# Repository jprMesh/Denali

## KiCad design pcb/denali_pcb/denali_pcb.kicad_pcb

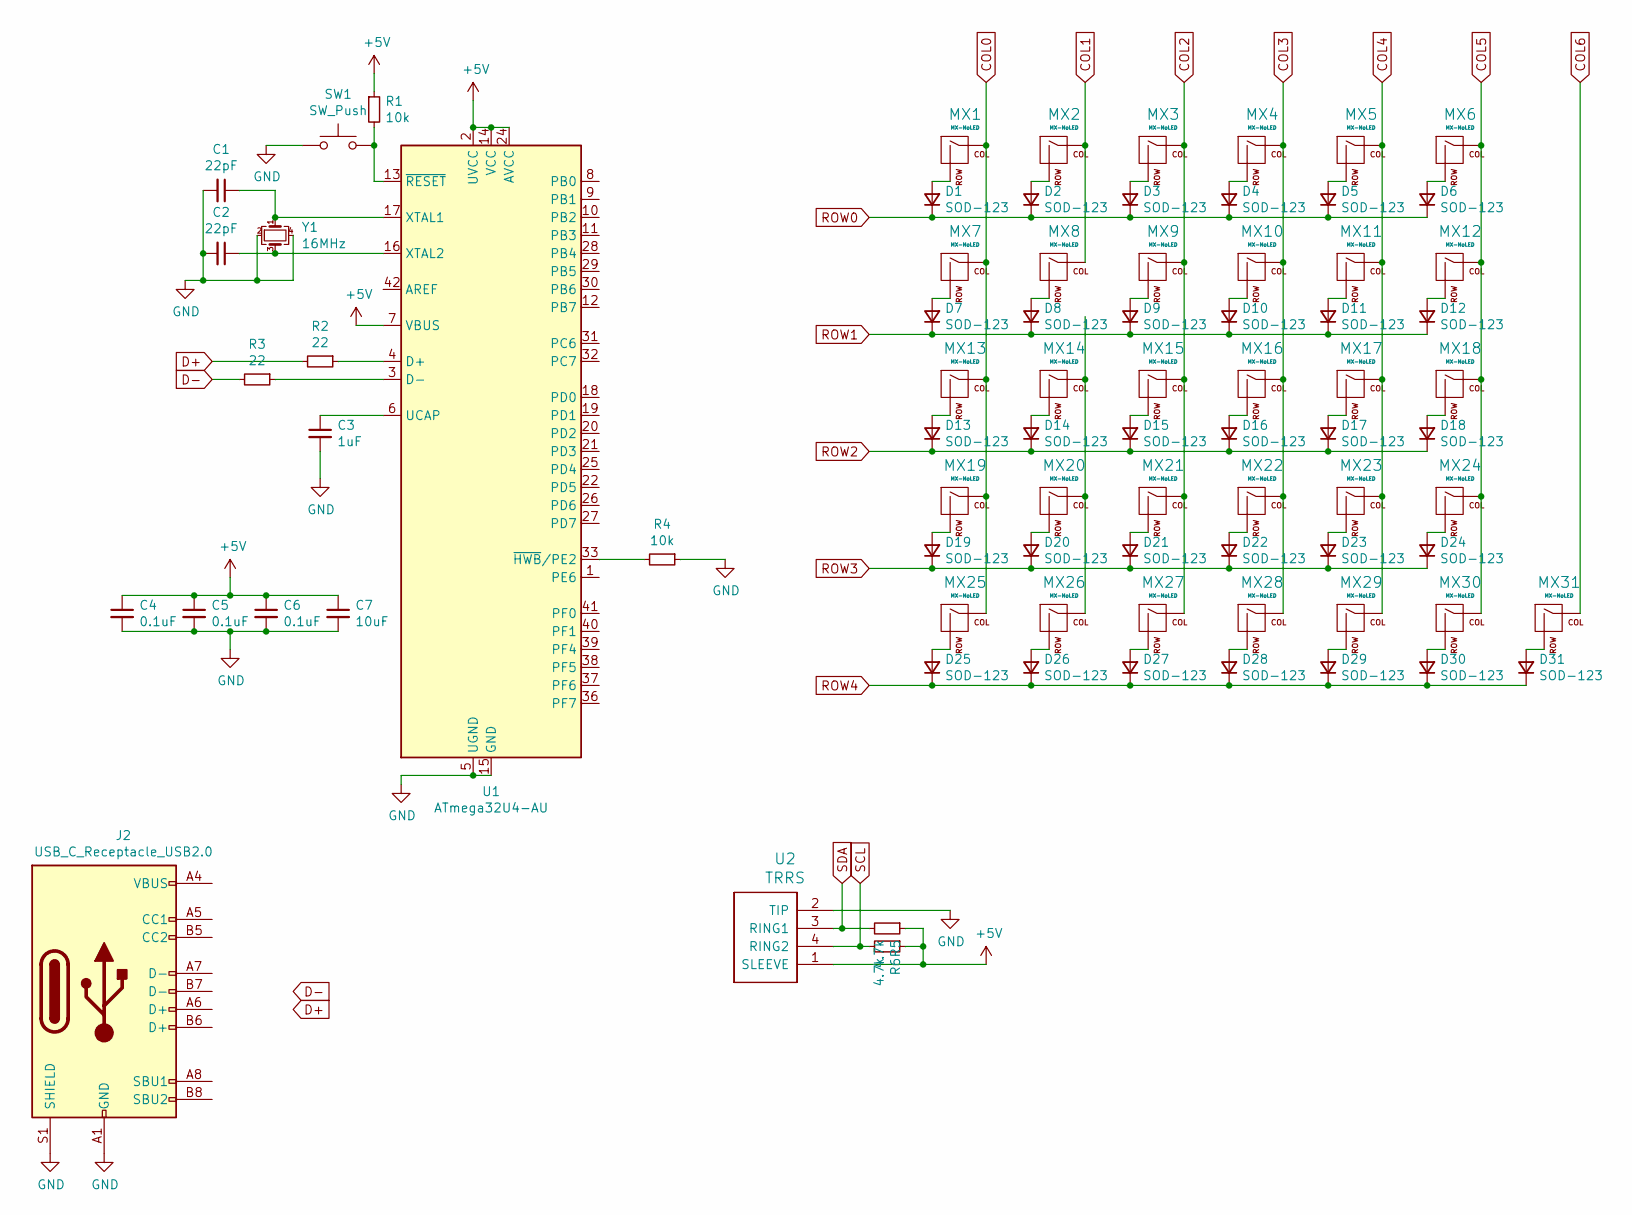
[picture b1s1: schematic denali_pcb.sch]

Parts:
C1, C2: 22pF; C_0805_2012Metric
C3: 1uF; C_0805_2012Metric
C4, C5, C6: 0.1uF; C_0805_2012Metric
C7: 10uF; C_0805_2012Metric
D1, D2, D3, D4, D5, D6, D7, D8, D9, D10, D11, D12, D13, D14, D15, D16, D17, D18, D19, D20, D21, D22, D23, D24, D25, D26, D27, D28, D29, D30, D31: SOD-123; Diode-hybrid-3pad
J2: USB_C_Receptacle_USB2.0; USB_C_Receptacle_MUP_U22401
MX1, MX2, MX3, MX4, MX5, MX6, MX7, MX8, MX9, MX10, MX11, MX12, MX13, MX14, MX15, MX16, MX17, MX18, MX19, MX20, MX21, MX22, MX23, MX24, MX25, MX26, MX27, MX28, MX29, MX30, MX31: MX-NoLED; Kailh_socket_PG1350_reversible
R1, R4: 10k; R_0805_2012Metric
R2, R3: 22; R_0805_2012Metric
R5, R6: 4.7k; R_0805_2012Metric
SW1: SW_Push; SKQG-1155865
U1: ATmega32U4-AU; TQFP-44_10x10mm_P0.8mm
U2: TRRS; TRRS-PJ-320A-dual
Y1: 16MHz; Crystal_SMD_3225-4Pin_3.2x2.5mm_HandSoldering

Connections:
+5V: C4.1, C5.1, C6.1, C7.1, R1.1, R5.1, R6.1, U1.2 (UVCC), U1.7 (VBUS), U1.14 (VCC), U1.24 (AVCC), U1.34 (VCC), U1.44 (AVCC), U2.1 (SLEEVE)
COL0: MX1.1 (COL), MX7.1 (COL), MX13.1 (COL), MX19.1 (COL), MX25.1 (COL)
COL1: MX2.1 (COL), MX8.1 (COL)
COL2: MX3.1 (COL), MX9.1 (COL), MX15.1 (COL), MX21.1 (COL), MX27.1 (COL)
COL3: MX4.1 (COL), MX10.1 (COL), MX16.1 (COL), MX22.1 (COL), MX28.1 (COL)
COL4: MX5.1 (COL), MX11.1 (COL), MX17.1 (COL), MX23.1 (COL), MX29.1 (COL)
COL5: MX6.1 (COL), MX12.1 (COL), MX18.1 (COL), MX24.1 (COL), MX30.1 (COL)
COL6: MX31.1 (COL)
D+: R2.2
D-: R3.2
GND: C1.2, C2.2, C3.2, C4.2, C5.2, C6.2, C7.2, J2.A1 (GND), J2.A12 (GND), J2.B1 (GND), J2.B12 (GND), J2.S1 (SHIELD), R4.1, SW1.1, U1.5 (UGND), U1.15 (GND), U1.23 (GND), U1.35 (GND), U1.43 (GND), U2.2 (TIP), Y1.2, Y1.4
unnamed: C1.1, U1.17 (XTAL1), Y1.1
unnamed: C2.1, U1.16 (XTAL2), Y1.3
unnamed: C3.1, U1.6 (UCAP)
unnamed: D1.2 (A), MX1.2 (ROW)
unnamed: D2.2 (A), MX2.2 (ROW)
unnamed: D3.2 (A), MX3.2 (ROW)
unnamed: D4.2 (A), MX4.2 (ROW)
unnamed: D5.2 (A), MX5.2 (ROW)
unnamed: D6.2 (A), MX6.2 (ROW)
unnamed: D7.2 (A), MX7.2 (ROW)
unnamed: D8.2 (A), MX8.2 (ROW)
unnamed: D9.2 (A), MX9.2 (ROW)
unnamed: D10.2 (A), MX10.2 (ROW)
unnamed: D11.2 (A), MX11.2 (ROW)
unnamed: D12.2 (A), MX12.2 (ROW)
unnamed: D13.2 (A), MX13.2 (ROW)
unnamed: D14.2 (A), MX14.2 (ROW)
unnamed: D15.2 (A), MX15.2 (ROW)
unnamed: D16.2 (A), MX16.2 (ROW)
unnamed: D17.2 (A), MX17.2 (ROW)
unnamed: D18.2 (A), MX18.2 (ROW)
unnamed: D19.2 (A), MX19.2 (ROW)
unnamed: D20.2 (A), MX20.2 (ROW)
unnamed: D21.2 (A), MX21.2 (ROW)
unnamed: D22.2 (A), MX22.2 (ROW)
unnamed: D23.2 (A), MX23.2 (ROW)
unnamed: D24.2 (A), MX24.2 (ROW)
unnamed: D25.2 (A), MX25.2 (ROW)
unnamed: D26.2 (A), MX26.2 (ROW)
unnamed: D27.2 (A), MX27.2 (ROW)
unnamed: D28.2 (A), MX28.2 (ROW)
unnamed: D29.2 (A), MX29.2 (ROW)
unnamed: D30.2 (A), MX30.2 (ROW)
unnamed: D31.2 (A), MX31.2 (ROW)
unnamed: J2.A4 (VBUS), J2.A9 (VBUS), J2.B4 (VBUS), J2.B9 (VBUS)
unnamed: MX14.1 (COL), MX20.1 (COL), MX26.1 (COL)
unnamed: R1.2, SW1.2, U1.13 (~RESET)
unnamed: R2.1, U1.4 (D+)
unnamed: R3.1, U1.3 (D-)
unnamed: R4.2, U1.33 (~HWB~/PE2)
ROW0: D1.1 (K), D2.1 (K), D3.1 (K), D4.1 (K), D5.1 (K), D6.1 (K)
ROW1: D7.1 (K), D8.1 (K), D9.1 (K), D10.1 (K), D11.1 (K), D12.1 (K)
ROW2: D13.1 (K), D14.1 (K), D15.1 (K), D16.1 (K), D17.1 (K), D18.1 (K)
ROW3: D19.1 (K), D20.1 (K), D21.1 (K), D22.1 (K), D23.1 (K), D24.1 (K)
ROW4: D25.1 (K), D26.1 (K), D27.1 (K), D28.1 (K), D29.1 (K), D30.1 (K), D31.1 (K)
SCL: R6.2, U2.4 (RING2)
SDA: R5.2, U2.3 (RING1)

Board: 2 copper layers, 80 parts (0 on the bottom side), 55 nets, no tracks yet.

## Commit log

2020-05-03 Initial commit with SCAD files and concept image
2020-05-03 PCB project created
2020-05-03 Gitignore created
2020-05-03 Add keyboard component footprint kicad libraries
2020-05-03 Linked kicad libraries to project
2020-05-06 schematic with footprints
2021-11-30 added hinge to cad
2021-12-03 parts list
2021-12-03 minor hinge adjustments and reorganize parts list
2021-12-03 move pcb stuff into dir
2021-12-03 add new footprint library for choc hotswap footprints
2021-12-03 schematic work
2021-12-03 remove bad footprint library
2021-12-03 switched footprint library
2021-12-03 updated footprints in schematic
2021-12-03 started placing components on pcb
2021-12-05 added rough pcb to cad
2022-02-03 parts
2022-02-03 pcb layout draft
2022-02-04 added trrs to schematic, no clue what's going on with the layout yet
2022-03-12 case changes and pcb resources
2022-03-13 more work on the case hinge
2022-03-13 rev 2.2 case
2022-03-15 fixed keyswitch ledge thickness
2022-03-15 hinge bottom, ID tuning to fit brass rods
2022-03-20 rp2040 kicad files I think...
2022-03-22 v2.3 case wide enough for rp2040-zero and added magnet holes
2022-03-23 firmware for handwire
2022-03-23 changes after final prototype:
    reduced key hole size, increased plate thickness, increased magnet bulge and hole size, adjusted rp2040zero placement and usb cutout
2022-03-24 final touches, backstop for mcu, backplate accomodation
2022-03-26 more case adjustments. press fit backplate.
2022-03-26 comments for stl exporting
2022-03-26 rev 2.4 stls
2022-04-03 hinge spacing and magnet hole spacing
2022-04-03 rev2.5 stls
2022-04-16 final fw after wiring up kb
2022-04-16 backplate for final case
2022-07-27 Initial commit of Olympus column stagger design
2022-07-27 moved usb connector
